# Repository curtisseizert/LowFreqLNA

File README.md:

# LowFreqLNA
A 0.01Hz-1+MHz low noise amplifier

Current Status
--------------
I have made two of these and have done a fair amount of testing to nail down root causes of some of the issues (see later in this readme) that have proven to be a bit of a nuisance. I am also moving things around a bit on the battery and battery charger boards to allow a board-to-board connection of the two and increase the clearance between the battery board and the amplifier board. I have also tested improvements to the input stage that significantly reduce the low frequency noise, lowering the 1/f corner to <1 Hz. These are detailed in the issues section #7.

1. Battery board revision: <b>complete</b>
2. Battery charger revision: <b>complete</b>
3. Low distortion buffer: back to drawing board
4. Main board revision: planning/schematic revision
5. BOM population: procrastinating

Introduction
------------

This repository contains the complete design files for a low noise AC coupled amplifier intended especially for characterization of 1/f noise of voltage references, DACs, etc. For broader applicability, it also has a reasonably high bandwidth of 2.5 MHz (measured, -3dB) at 60 or 80 dB gain, and about 1 MHz at 100 dB gain. Consistent with my primary use case for this amplifier, it has exceptionally low 1/f noise itself (measured at 3.2 nVRMS from 0.01-10 Hz) and a low broadband noise density of around 0.6 nV/rtHz. The quiescent current draw for the amplifier is about 30 mA, giving it a battery life of >100 h with the 4S 21700 Li batteries used to power the device. The project includes five PCBs:
(1) The main amplifier board
(2) The BMS board
(3) The SW board
(4) The front panel board
(5) The rear panel board/battery charger.

At present, I have hand assembled these using a converted toaster oven, which is a semi-onerous but doable-in-a-weekend task. As such, the BOMs are incomplete in all cases, which I will aim to rectify going forward. It is my hope that this will serve the needs of others designing voltage references, DACs, power supplies, etc. I may try to fix a couple things about this that have been bugging me, such as the lack of prefiltering and the antenna-like properties of the PP caps used in HP filters in the signal train. There is also a bit of room for reducing current draw. A fully differential version has been suggested, but if I work on that, I will make a separate repository for it.

The input stage is formed from a 24uF/100M RC high pass filter feeding a hybrid amplifier. The hybrid amplifier consists of 16 parallel JFE2140 dual JFETs in a cascode differential amplifier configuration. This drives an OPA140 op amp, which provides feedback via a 1k/2R divider to the inverting gate of the differential pair. The DC offset of the input stage is removed with a 2.2uF/10M HP filter. A switched gain stage amplifies the signal, which is HP filtered again to remove offsets and set the high-pass cutoff of the amplifier. The switched low-pass filtering is provided by two fourth-order butterworth filters in Sallen-Key topology. Switches select either one of these outputs or the unfiltered amplified signal to feed to the output stage.

A common problem with low-frequency AC coupled amplifiers is very long settling times when switching inputs. This is addressed with the "SETTLE" and "IN PROT" (Input protection) switches on the front panel. The former shorts the resistors of both of the post-input stage HP filter outputs with low-leakage MMBF4117 JFETs, and the latter shorts the input AC coupling filter by shorting the 100M resistor with a relay. The "IN PROT" switch also places a 6k04 resistor in series with the AC coupling filter to avoid large transients when switching between sources with different DC biases. With these switches, it is possible to take valid measurements down to 0.1 Hz with a minute or so of settling time and measurements down to 0.01 Hz with 5-10 minutes of settling time. Saturation of the amplifiers prior to both HP filters is detected with window comparators, which drive warning lights on the front panel. These features are meant to make it reasonably convenient to make low-level measurements and be confident the result is valid.

Electrical Characteristics
--------------------------

The following characteristics are taken from the one of these that I have fully assembled. Characterization was performed with a Digilent Analog Discovery Pro ADP3450 for bandwidths >10 kHz, a Keysight 34465A, and an HP3458A. Noise captures with the ADP3450 were digitized in Waveforms, exported, and transformed to the frequency domain using the SciPy Signal Python library in Spyder IDE. Captures with the HP3458A were taken using the PyVISA Python library for low frequency (50 SPS) digitization. The HP3458A was used for most low frequency work due to its superior isolation and common mode immunity. Bandwidth characterization was performed with the network analyzer utility in Waveforms for the ADP3450 and a 60dB attenuator. Gain calibration was performed by measuring the noise of a 6k04 resistor (9.97 nV/rtHz Johnson-Nyquist voltage noise density at 298k) comparing the bandwidth-limited RMS amplitude of the output signal to the theoretical value at the ambient temperature outside the amplifier. Linearity was checked by obtaining bandwidth-limited RMS amplitudes for a 240R resistor and a short, accounting for the RMS addition of the amplifier's own noise floor and that of the 240R resistor. The calibration resistors were 0.1%, 10 ppm/K thin film types. Quiescent current was measured by powering the amplifier with a Rigol DP832A DC power supply at +/-8V.

<table>
  <tr><td><b>Parameter</td><td><b>Condition</td><td><b>Result</td><td><b>Comment</td></tr>
  <tr><td>Voltage Noise Density</td><td>1 MHz</td><td>0.6 nV/rtHz</td><td>A</td></tr>
  <tr><td> </td><td>1 kHz</td><td>0.64 nV/rtHz</td><td>A</td></tr>
  <tr><td> </td><td>10 Hz</td><td>0.75 nV/rtHz</td><td>B</td></tr>
  <tr><td> </td><td>1 Hz</td><td>1.2 nV/rtHz</td><td>C</td></tr>
  <tr><td> </td><td>0.1 Hz</td><td>3.1 nV/rtHz</td><td>C</td></tr>
  <tr><td> </td><td>0.01 Hz</td><td>13.4 nV/rtHz</td><td>C,D</td></tr>
  <tr><td>Voltage Noise</td><td>0.1 Hz - 10 Hz</td><td>15 nV p-p</td><td>C</td></tr>
  <tr><td></td><td>0.01 Hz - 10 Hz</td><td>20 nV p-p</td><td>C</td></tr>
  <tr><td>Current Noise Density</td><td>0.1-1 Hz</td><td><2 fA/rtHz</td><td>E</td></tr>
  <tr><td>Input stage bias current</td><td></td><td>2.7 pA</td><td>F</td></tr>
  <tr><td>Input stage offset voltage</td><td></td><td>-94 uV</td><td>G</td></tr>
  <tr><td>-3dB Bandwidth</td><td>0R source impedance</td><td>2.8 MHz</td><td></td></tr>
  <tr><td>Input Capacitance</td><td>6k04 source impedance</td><td>140 pF</td><td>H</td></tr>
  <tr><td>10 kHz Low pass filter</td><td></td><td>4th order Butterworth</td><td></td></tr>
  <tr><td>10 Hz Low pass filter</td><td></td><td>4th order Butterworth</td><td></td></tr>
  <tr><td>THD</td><td>5 kHz</td><td><-70dB</td><td></td></tr>
  <tr><td>Quiescent Current</td><td>shorted input</td><td>30 mA</td><td></td></tr>
  <tr><td>Battery Capacity</td><td>Samsung 50S cells</td><td>5000 mA/h</td><td>nominal</td></tr>
  <tr><td>i_chg</td><td></td><td>2.7A</td><td></td></tr>
  <tr><td>Charger efficiency</td><td>V_Batt = 15V</td><td>98%</td><td>I</td></tr>
</table>

A: Full bandwidth, ADP-3450; B: 0.1-10 kHz bandwidth, ADP-3450; C: 0.01-10 Hz bandwidth, HP3458A; D: calc'd from measured value (9.5 nV/rtHz) and 3dB attenuation from HP filter; E: Calculated from open input VSD (100M resistor). Resulting noise was <0.1% from calculated value; F: Calculated from difference in offset voltage between 0R and 100M resistance to GND for input gate; G: Input gate shorted to GND; H: -3dB point with 6k04 resistor is 190 kHz. Primarily from board parasitics and RC damper; I: Measured on board, does not include cable losses

Spectra
-------

Application: Measuring voltage noise of voltage references
----------------------------------------------------------
Due to the low noise floor of the preamplifier, it can be used to easily measure the voltage noise of even the quietest (room temperature) references without error due to its own noise floor. Additionally, the use of polypropylene AC coupling capacitors with low dielectric absorption and the inclusion of the "SETTLE" feature allow measurement down to 10 mHz without excessive settling time. The plot below shows the voltage noise spectral density of several ADR1000-based 10-V references. Due to the high input impedance at low frequency, increasing the source impedance does not measurably change the gain of the amplifier. This is not the case with common 1000 uF/1k AC-coupled LNAs, which give considerable gain errors at even moderate source impedances (e.g., a 100 Ohm source impedance would give a gain error of 9.1%).

Issues
------

1. Input capacitance is higher than I'd like, which reduces the bandwidth with high impedance sources. Some of the capacitance is from board parasitics (ca. 100 pF), and some is from the R-C damper that is necessary to damp out oscillations with inductive sources (including most precision op amps). My plan to deal with this in the next revision is to modify the layout to reduce the board parasitics and switch in the R-C damper with an additional relay. Very little of the input capacitance is due to large Ciss of the paralleled JFETs as most of this presents as common mode capacitance and is bootstrapped by feedback. My target for input capacitance (with no R-C damper switched in) is 50 pF, but this is a lower priority than stability.
2. Second order (mostly) harmonic distortion of the ADA4622-2 buffer following the final HP filter stage leads to a DC offset term in the output. This is worst around 2 MHz and gets considerably worse with increasing ammplitude of the high frequency tone (it varies directly with the fourth power of the amplitude). The JFET switches are not a major issue (when SETTLE is off), which I have tested by removing them from the board. When SETTLE is on, it is worse, which negatively impacts settling time. As such, a 1 MHz sine wave amplitude modulated at 0.1 Hz will appear after 10 Hz LP filtering as a 0.1 Hz signal and harmonics, which is bad. The approach to this will be twofold: prefiltering and a composite buffer. Prefiltering will be described in #3. The composite buffer is a solution to a problem of a difficult convergence of design constraints: this buffer must have low Ib and current noise, reasonable common mode range (>+/-2.5V with 5.5V and -4.3V rails), low distortion at high frequency, and ability to operate on 10V total supply voltage with low quiescent current. To my knowledge, there are no monolithic amplifiers that satisfy these constraints. Without the high frequency distortion issue, only the ADA4622, OPAx191, and OPAx192 were good choices to my knowledge, but all of these led to the distortion-induced offset issue. In simulation, a dual JFET follower feeding an ADA4805 does well with a total quiescent current of about 1.1 mA and <0.1 dB peaking. I will prototype this block and test it before committing to the design for the next revision.
3. Amplifying signals at full bandwidth limits dynamic range for LF noise analyses. I will address this by filtering prior to the final gain stages, probably with a single-pole RC filter. Another solution would be to have the LP filter stages operate at gain >1, but I would prefer not to take this tack because it would mean the gain error of the amplifier is dependent on which LP filter stage is switched in.
4. Input protection switching is inconsistent due to contact bounce. I did not think this would be an issue with the one-shots used for relay switching, but it is. For now, connecting the K1_SW signal to both GND and 3V3 with 22k resistors does the trick, but this is not ideal, so I will implement a more robust dual-inverter debounce block for all the relay switches. In practice, however, only K1 seems to be affected by this issue due to it being switched differently on the front panel.
5. The 0804 (4x0402) resistor arrays are a PITA and almost always need to be fixed after reflow, so I'll replace those with 1206 (4x0603) arrays.
6. The 2.2 uF PP caps used in the HP filters seem to radiate, which requires shielding the input HP filter caps (these need to be PP for leakage). This shielding increases input capacitance (to ground), so I will replace the 2.2 uF caps with a few paralleled 470nF C0G capacitors, which have sufficiently low leakage to nullify the modest DC offsets following each stage, even with low frequency breakpoints.
7. The low frequency noise of the input stage is negatively impacted by the current noise of the mirror transistors. The fact that the low frequency noise is sub-optimal is evident from low frequency noise measurements of a pair of JFE2140s configured as source followers biased to the same drain current as a pair in the input stage. Because there are 16 such pairs in the LNA, the ratio of the NSD curves for this DUT and the noise floor should give a flat SNR of 12 dB, but this was not the case in the current revision. The most likely culprits to investigate were current noise from the NPN cascode transistor pair and current noise from the PNP current mirror transistor pair. Tests of the low frequency current noise of the NPN pair showed it was an unlikely culprit, accounting for perhaps 2% of the noise density at 10 mHz. Deletion of the current mirror pair, however, resolved the issue without any ill effects. This part was superfluous because the load seen by the collectors of the NPN cascode pair is the current mirror (or resistive loads) in parallel with 1/gm of the PNP folded cascode pair. With a collector current of ca. 100 uA, 1/gm is about 250R. With 330R resistive loads (i.e., shorting the collectors and emitters of the mirror transistors), the load drops from ~250R to ~142R, which still allows sufficiently high voltage gain at the emitters of the PNP pair to ensure they do not add significant noise. The effect of this modification on the low frequency noise is shown below.

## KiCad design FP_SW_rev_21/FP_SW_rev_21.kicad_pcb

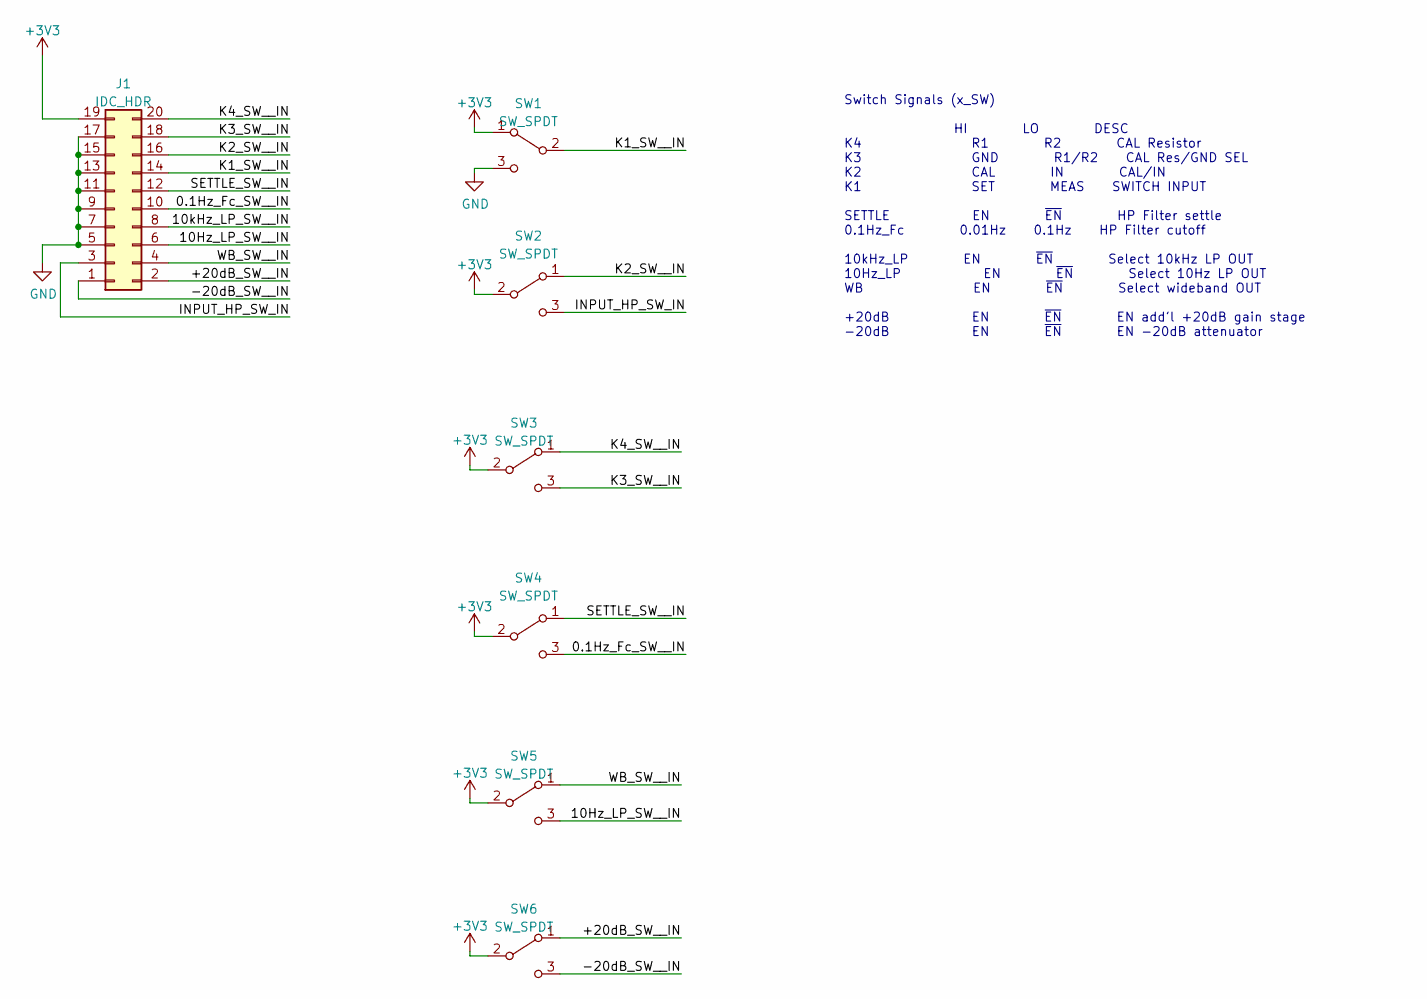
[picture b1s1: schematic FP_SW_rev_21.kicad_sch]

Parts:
J1: IDC_HDR; PinHeader_2x10_P1.27mm_Vertical
SW1, SW2, SW3, SW4, SW5, SW6: SW_SPDT; SW_SPDT_4.7_mm

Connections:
+3V3: J1.19, SW1.1 (A), SW2.2 (B), SW3.2 (B), SW4.2 (B), SW5.2 (B), SW6.2 (B)
/0.1Hz_Fc_SW__IN: J1.10, SW4.3 (C)
/10Hz_LP_SW__IN: J1.6, SW5.3 (C)
/10kHz_LP_SW__IN: J1.8
/+20dB_SW__IN: J1.2, SW6.1 (A)
/-20dB_SW__IN: J1.1, SW6.3 (C)
/INPUT_HP_SW_IN: J1.3, SW2.3 (C)
/K1_SW__IN: J1.14, SW1.2 (B)
/K2_SW__IN: J1.16, SW2.1 (A)
/K3_SW__IN: J1.18, SW3.3 (C)
/K4_SW__IN: J1.20, SW3.1 (A)
/SETTLE_SW__IN: J1.12, SW4.1 (A)
/WB_SW__IN: J1.4, SW5.1 (A)
GND: J1.5, J1.7, J1.9, J1.11, J1.13, J1.15, J1.17, SW1.3 (C)

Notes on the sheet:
Switch Signals (x_SW) HI LO DESC K4 R1 R2 CAL Resistor K3 GND R1/R2 CAL Res/GND SEL K2 CAL IN CAL/IN K1 SET MEAS SWITCH INPUT SETTLE EN ~{EN} HP Filter settle 0.1Hz_Fc 0.01Hz 0.1Hz HP Filter cutoff 10kHz_LP EN ~{EN} Select 10kHz LP OUT 10Hz_LP EN ~{EN} Select 10Hz LP OUT WB EN ~{EN} Select wideband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

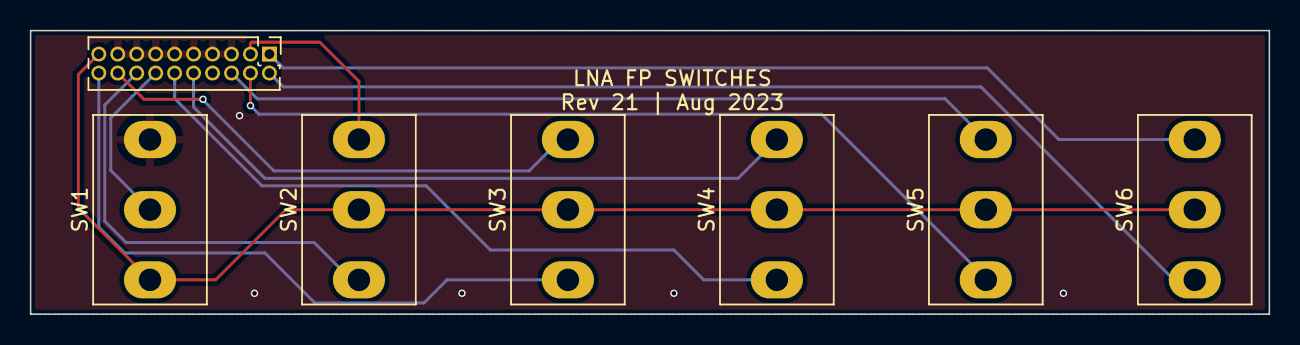
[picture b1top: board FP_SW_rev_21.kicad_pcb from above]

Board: 2 copper layers, 83.0 x 19.0 mm, 7 parts (0 on the bottom side), 13 nets.

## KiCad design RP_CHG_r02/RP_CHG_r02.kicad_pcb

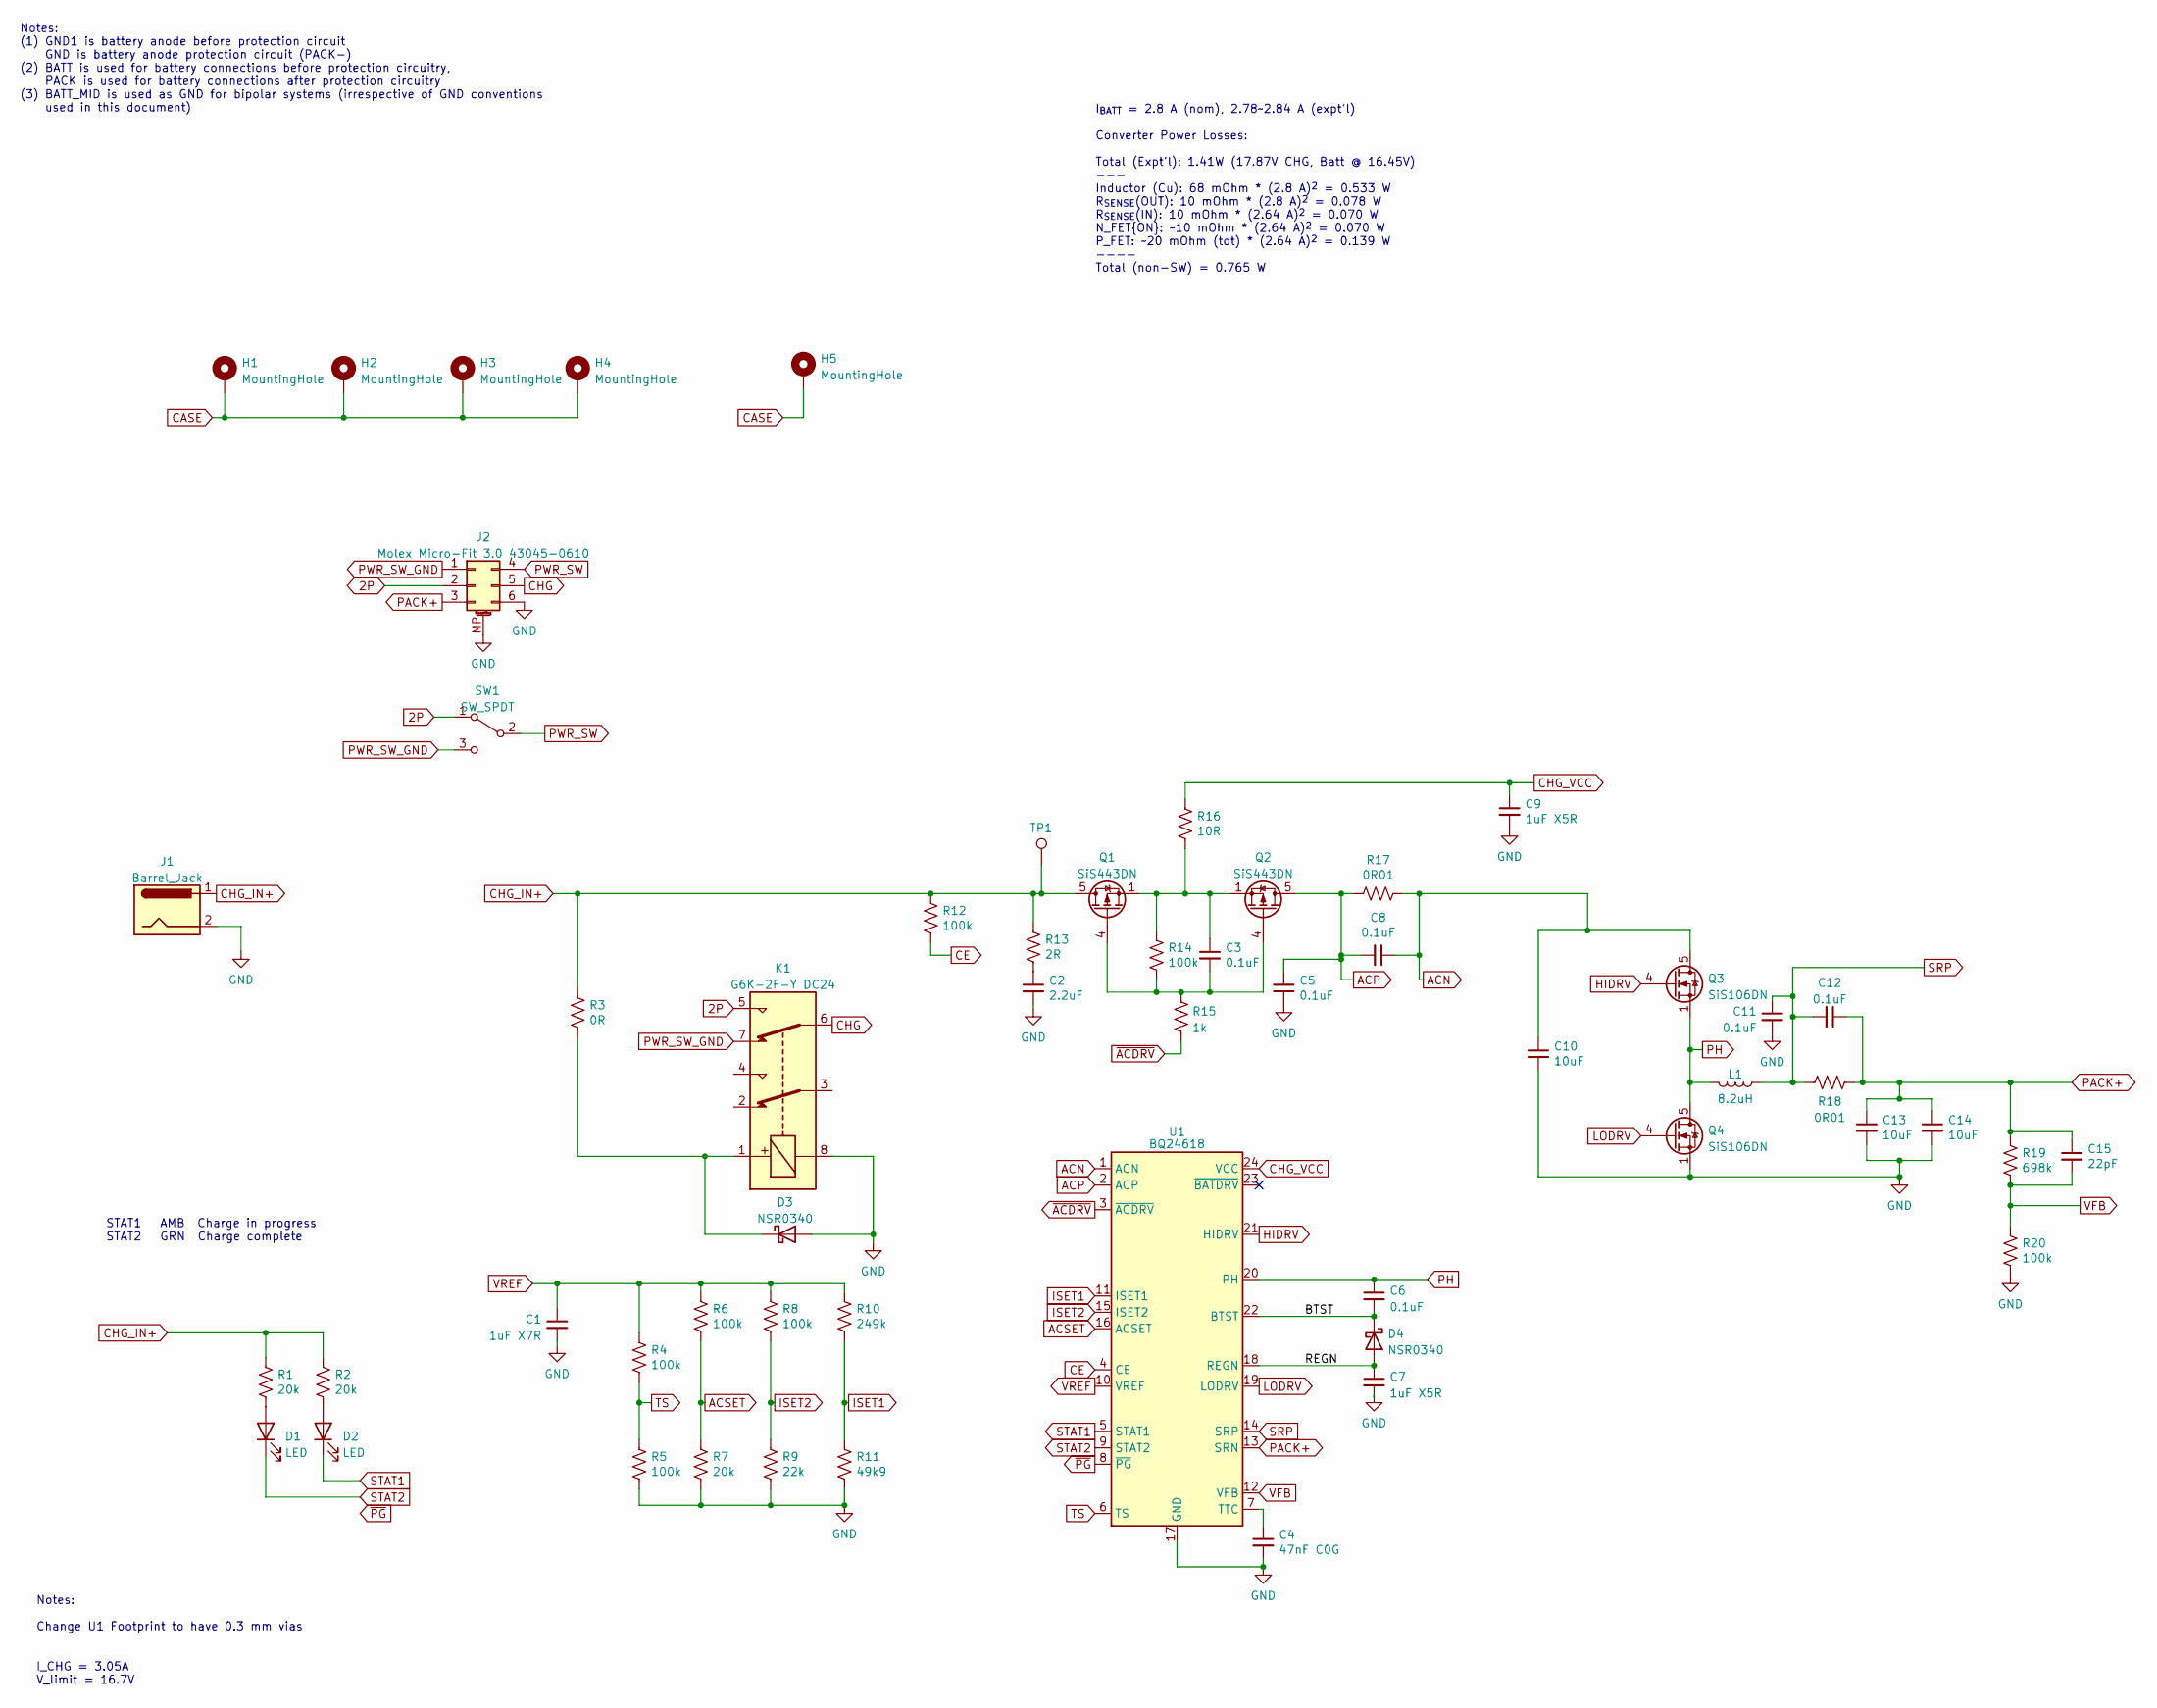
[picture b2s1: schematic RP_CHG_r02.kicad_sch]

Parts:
C1: 1uF X7R; C_0603_1608Metric_red_outline
C2: 2.2uF; C_1206_3216Metric_Red
C3, C5, C6, C8, C11, C12: 0.1uF; C_0402_1005Metric
C4: 47nF C0G; C_0805_2012Metric_Red_outline
C7, C9: 1uF X5R; C_0402_1005Metric
C10: 10uF; C_1210_3225Metric
C13, C14: 10uF; C_1206_3216Metric_Red
C15: 22pF; C_0603_1608Metric_red_outline
D1, D2: LED; LED_Osram_Lx_P47F_D2mm_ReverseMount
D3, D4: NSR0340; D_SOD-523
H1, H2, H3, H4: MountingHole; MountingHole_4.3mm_M4_ISO14580_Pad
H5: MountingHole; PanelCutout_6.5mm_PTH
J1: Barrel_Jack; BarrelJackDC_Switchcraft721_712
J2: Molex Micro-Fit 3.0 43045-0610; Molex_Micro-Fit_3.0_43045-0610_2x03-1MP_P3.00mm_Horizontal
K1: G6K-2F-Y DC24; Relay_DPDT_Omron_G6K-2F-Y
L1: 8.2uH; L_Vishay_IHLP-2525
Q1, Q2: SiS443DN; Vishay_PowerPAK_1212-8_Single
Q3, Q4: SiS106DN; Vishay_PowerPAK_1212-8_Single
R1, R2, R7: 20k; R_0402_1005Metric
R3: 0R; R_0603_1608Metric_red
R4, R5, R6, R8, R12, R14, R20: 100k; R_0402_1005Metric
R9: 22k; R_0402_1005Metric
R10: 249k; R_0402_1005Metric
R11: 49k9; R_0402_1005Metric
R13: 2R; R_0603_1608Metric_red
R15: 1k; R_0402_1005Metric
R16: 10R; R_0603_1608Metric_red
R17, R18: 0R01; R_1206_3216Metric
R19: 698k; R_0402_1005Metric
SW1: SW_SPDT; TestPoint_3Pads
TP1: TestPoint; TestPoint_Pad_D1.0mm
U1: BQ24618; HVQFN-24-1EP_4x4mm_P0.5mm_EP2.5x2.5mm

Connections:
2P: J2.2, K1.5, SW1.1 (A)
/BTST: C6.2, D4.1 (K), U1.22 (BTST)
/REGN: C7.1, D4.2 (A), U1.18 (REGN)
ACN: C8.1, C10.1, Q3.5 (D), R17.1, U1.1 (ACN)
ACP: C5.2, C8.2, Q2.5 (D), R17.2, U1.2 (ACP)
ACSET: R6.2, R7.1, U1.16 (ACSET)
CASE: H1.1, H2.1, H3.1, H4.1, H5.1
CE: R12.2, U1.4 (CE)
CHG: J2.5, K1.6
CHG_IN+: J1.1, Q1.5 (D), R1.1, R2.1, R3.2, R12.1, R13.1, TP1.1
CHG_VCC: C9.1, R16.2, U1.24 (VCC)
EP: C1.2, C2.2, C4.2, C5.1, C7.2, C9.2, C10.2, C11.2, C13.2, C14.2, D3.2 (A), J1.2, J2.6, J2.MP (MountPin), K1.8, Q4.1 (S), Q4.2 (S), Q4.3 (S), R5.2, R7.2, R9.2, R11.2, R20.1, U1.17 (GND), U1.25 (EP)
HIDRV: Q3.4 (G), U1.21 (HIDRV)
ISET1: R10.2, R11.1, U1.11 (ISET1)
ISET2: R8.2, R9.1, U1.15 (ISET2)
LODRV: Q4.4 (G), U1.19 (LODRV)
unnamed: C2.1, R13.2
unnamed: C3.1, Q1.1 (S), Q1.2 (S), Q1.3 (S), Q2.1 (S), Q2.2 (S), Q2.3 (S), R14.1, R16.1
unnamed: C3.2, Q1.4 (G), Q2.4 (G), R14.2, R15.1
unnamed: C4.1, U1.7 (TTC)
unnamed: D1.2 (A), R1.2
unnamed: D2.2 (A), R2.2
unnamed: D3.1 (K), K1.1, R3.1
PACK+: C12.1, C13.1, C14.1, C15.1, J2.3, R18.1, R19.2, U1.13 (SRN)
PH: C6.1, L1.2, Q3.1 (S), Q3.2 (S), Q3.3 (S), Q4.5 (D), U1.20 (PH)
PWR_SW: J2.4, SW1.2 (B)
PWR_SW_GND: J2.1, K1.7, SW1.3 (C)
SRP: C11.1, C12.2, L1.1, R18.2, U1.14 (SRP)
STAT1: D2.1 (K), U1.5 (STAT1)
STAT2: D1.1 (K), U1.9 (STAT2)
TS: R4.2, R5.1, U1.6 (TS)
VFB: C15.2, R19.1, R20.2, U1.12 (VFB)
VREF: C1.1, R4.1, R6.1, R8.1, R10.1, U1.10 (VREF)
~ACDRV: R15.2, U1.3 (~ACDRV)
~PG: U1.8 (~PG)

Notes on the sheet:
I_{BATT} = 2.8 A (nom), 2.78~2.84 A (expt'l) Converter Power Losses: Total (Expt'l): 1.41W (17.87V CHG, Batt @ 16.45V) --- Inductor (Cu): 68 mOhm * (2.8 A)^{2} = 0.533 W R_{SENSE}(OUT): 10 mOhm * (2.8 A)^{2} = 0.078 W R_{SENSE}(IN): 10 mOhm * (2.64 A)^{2} = 0.070 W N_FET{ON}: ~10 mOhm * (2.64 A)^{2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
I_CHG = 3.05A V_limit = 16.7V
Notes: (1) GND1 is battery anode before protection circuit GND is battery anode protection circuit (PACK-) (2) BATT is used for battery connections before protection circuitry, PACK is used for battery connections after protection circuitry (3) BATT_MID is used as GND for bipolar systems (irrespect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
STAT1 AMB Charge in progress STAT2 GRN Charge complete
Notes: Change U1 Footprint to have 0.3 mm vias

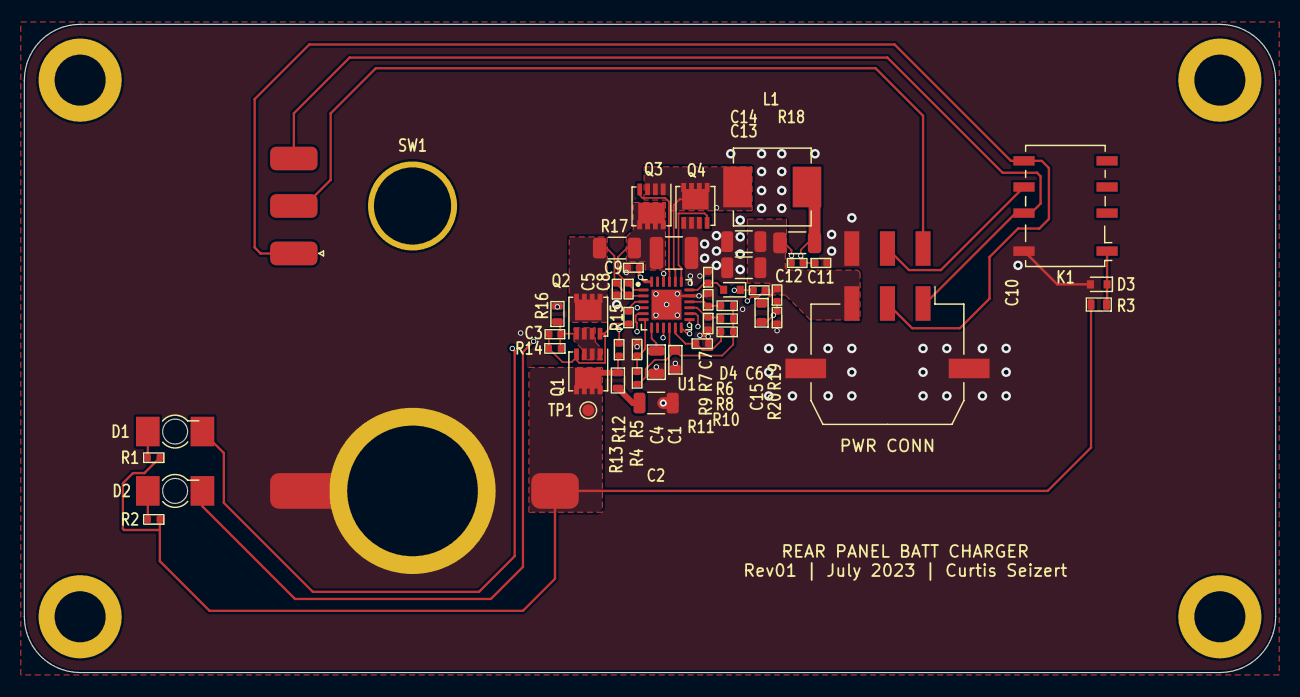
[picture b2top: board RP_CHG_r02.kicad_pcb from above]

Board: 4 copper layers, 105.4 x 54.6 mm, 55 parts (0 on the bottom side), 34 nets.

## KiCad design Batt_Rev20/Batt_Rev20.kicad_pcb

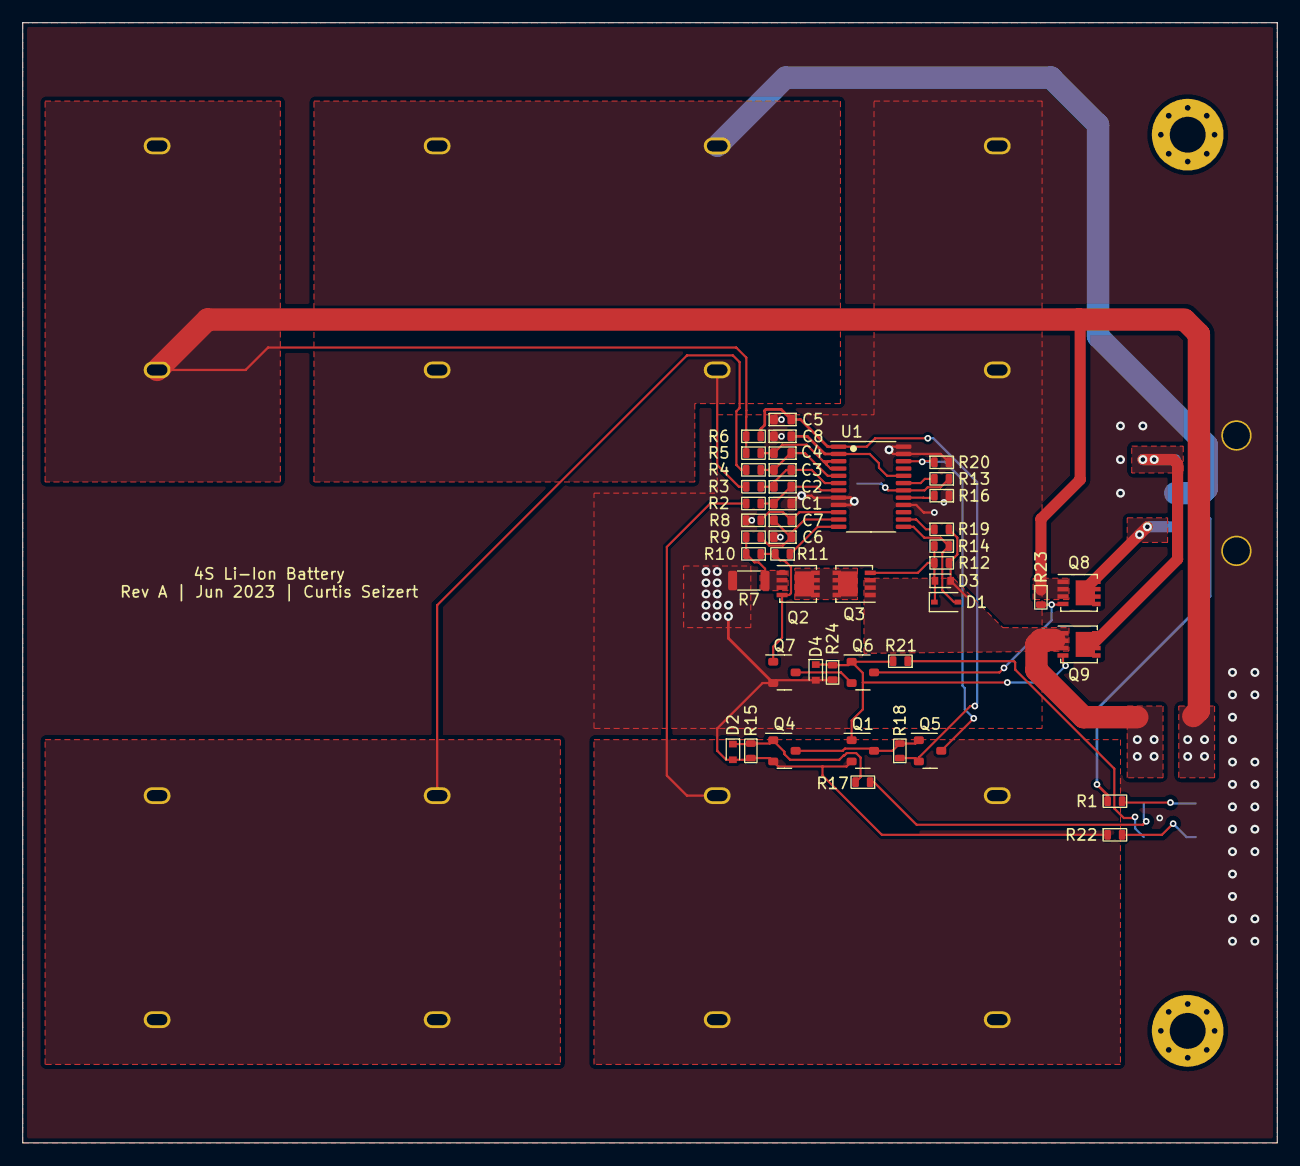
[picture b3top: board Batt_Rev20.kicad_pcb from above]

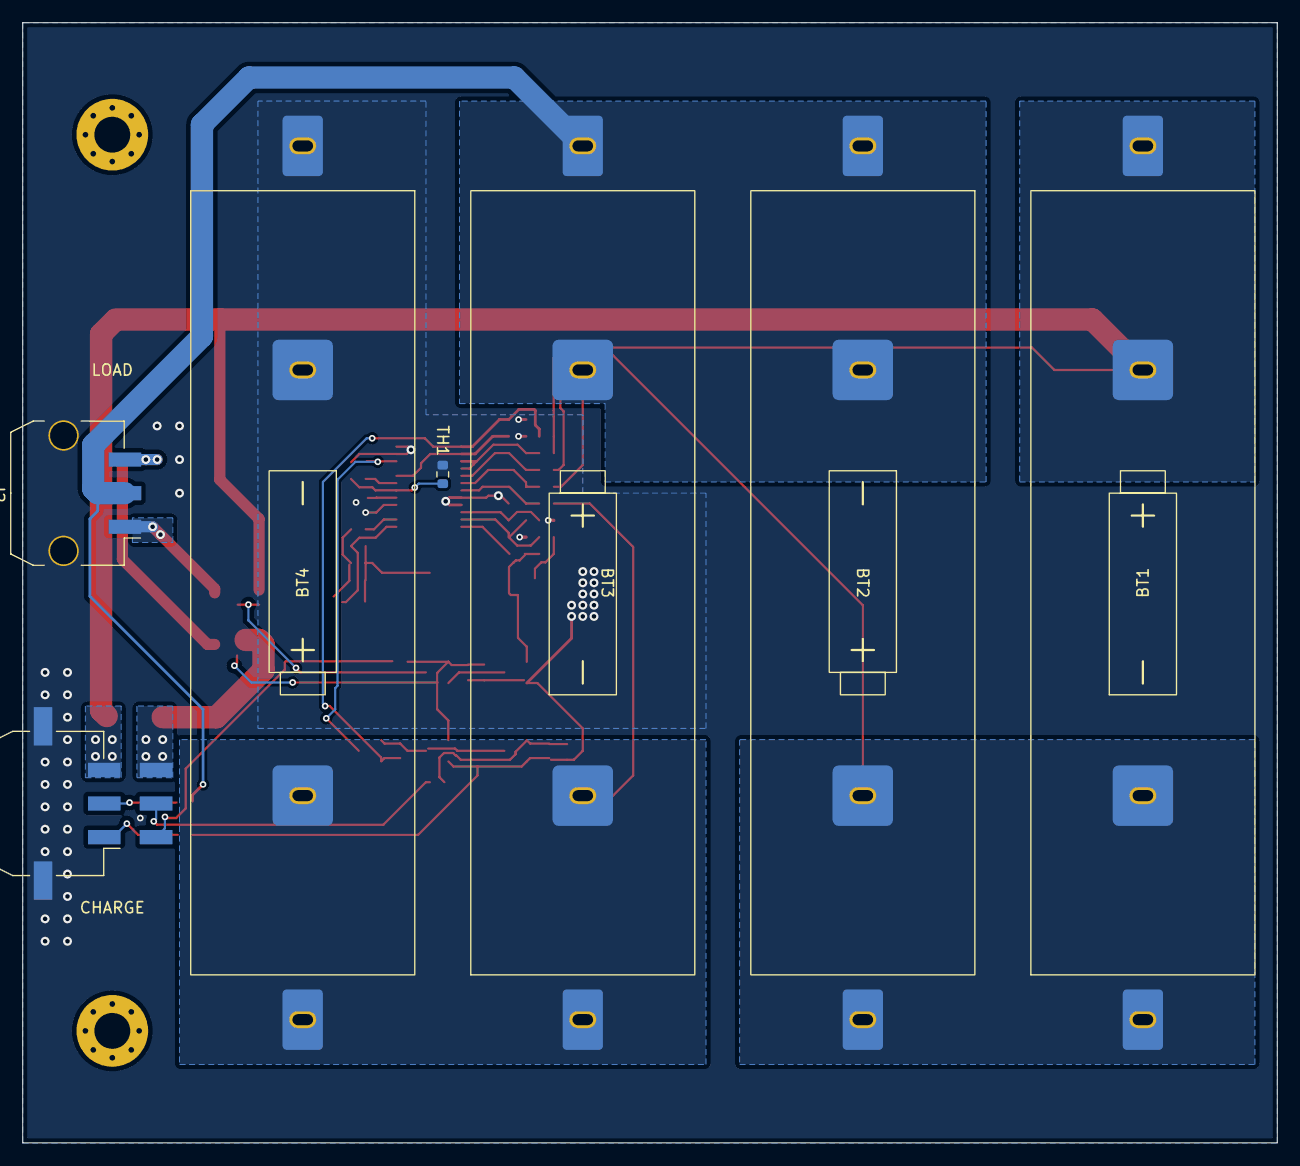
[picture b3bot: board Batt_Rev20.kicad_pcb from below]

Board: 2 copper layers, 112.0 x 100.0 mm, 56 parts (7 on the bottom side), 37 nets.

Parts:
BT1, BT2, BT3, BT4: Battery_Cell; BatteryHolder_Keystone246_21700
C1, C2, C3, C4, C5, C8: 1uF; C_0603_1608Metric_red_outline
C6, C7: 0.1uF; C_0603_1608Metric_red_outline
D1: RB751V40; D_SOD-323
D2, D3, D4: DZ2S100X0L; D_SOD-523
H1, H2: MountingHole; MountingHole_3.2mm_M3_Pad_Via
J1: Molex Micro-Fit 3.0 43045-0610; Molex_Micro-Fit_3.0_43045-0610_2x03-1MP_P3.00mm_Horizontal
J2: Micro-Fit 3.0 43650-0310; Molex_Micro-Fit_3.0_43650-0310_1x03-1MP_P3.00mm_Horizontal
NT1: Net-Tie_2; NetTie-2_SMD_Pad0.2mm
Q1, Q4, Q6, Q7: BSS123; SOT-23
Q2, Q3, Q9: SiS862ADN; Vishay_PowerPAK_1212-8_Single
Q5: BSS84; SOT-23
Q8: SiS443DN; Vishay_PowerPAK_1212-8_Single
R1, R6, R11, R14, R21, R22: 1k; R_0603_1608Metric_red
R2, R3, R4, R5: 33R; R_0603_1608Metric_red
R7: 0R01; R_1206_3216Metric_red
R8, R9: 100R; R_0603_1608Metric_red
R10, R12, R15, R18, R20, R23, R24: 1M; R_0603_1608Metric_red
R13, R17: 10k; R_0603_1608Metric_red
R16: 100k; R_0603_1608Metric_red
R19: 470k; R_0603_1608Metric_red
TH1: 103-AT; R_0603_1608Metric
U1: BQ77915-08; TSSOP-24_4.4x7.8mm_P0.65mm

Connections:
1P: BT3.1 (-), BT4.2 (+), R2.1
2P: BT2.1 (-), BT3.2 (+), J2.2, R1.1, R3.1
3P: BT1.1 (-), BT2.2 (+), R4.1
4P: NT1.2, R5.1, R6.1
/CHG_FET_G: D1.1 (K), D3.1 (K), Q3.4 (G), R12.1, R14.2
/DSG_FET_G: Q2.4 (G), Q7.1 (G), R10.1, R11.2
/PRES: Q5.3 (D), R20.1, U1.22 (PRES)
AVDD: C8.1, U1.2 (AVDD), U1.20 (CCFG)
BATT-: BT4.1 (-), C1.1, C5.2, C6.1, C8.2, D2.2 (A), D4.2 (A), J1.MP (MountPin), J2.MP (MountPin), Q1.2 (S), Q4.2 (S), Q7.2 (S), R7.1, R8.1, R15.2, R16.1, R20.2, R22.1, R24.2, TH1.2, U1.8 (VC0), U1.9 (VSS), U1.16 (CBI), U1.23 (CTRC), U1.24 (CTRD)
CHG: J1.5, R17.1
NMOS_G: D4.1 (K), Q1.1 (G), Q6.1 (G), Q9.4 (G), R21.2, R24.1
unnamed: C1.2, C2.1, R2.2, U1.7 (VC1)
unnamed: C2.2, C3.1, R3.2, U1.6 (VC2)
unnamed: C3.2, C4.1, R4.2, U1.5 (VC3)
unnamed: C4.2, R5.2, U1.3 (VC5), U1.4 (VC4)
unnamed: C6.2, C7.1, R9.1, U1.11 (SRN)
unnamed: C7.2, R8.2, U1.10 (SRP)
unnamed: D1.2 (A), R14.1, U1.13 (CHG)
unnamed: D2.1 (K), Q4.1 (G), R15.1, R17.2
unnamed: Q2.1 (S), Q2.2 (S), Q2.3 (S), R7.2, R9.2, R10.2
unnamed: Q2.5 (D), Q3.5 (D)
unnamed: Q1.3 (D), Q4.3 (D), Q5.1 (G), R18.2
unnamed: Q6.3 (D), Q8.4 (G), R23.2
unnamed: Q6.2 (S), Q7.3 (D)
unnamed: J1.2, R1.2
unnamed: R11.1, U1.12 (DSG)
unnamed: R13.1, TH1.1, U1.18 (TS)
unnamed: R13.2, U1.19 (VTB)
unnamed: R16.2, U1.17 (OCDP)
unnamed: R19.1, U1.14 (LD)
PACK+: BT1.2 (+), J1.3, NT1.1, Q8.1 (S), Q8.2 (S), Q8.3 (S), R23.1
PACK-: D3.2 (A), J1.6, Q3.1 (S), Q3.2 (S), Q3.3 (S), Q9.1 (S), Q9.2 (S), Q9.3 (S), R12.2, R19.2
PWR_SW: J1.4, R21.1
PWR_SW_GND: J1.1, R22.2
VDD: C5.1, Q5.2 (S), R6.2, R18.1, U1.1 (VDD)
V_{OUT}+: J2.1, Q8.5 (D)
V_{OUT}-: J2.3, Q9.5 (D)

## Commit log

2023-10-14 Second Commit
2023-10-14 Uploaded photos
2023-10-14 Update README.md
    Added picture
2023-11-09 Update README.md
    Added current status and issues sections, updated electrical characteristics with more extensive testing.
2023-11-12 Update README.md
    Fixed some typos and added status of individual tasks for next revision.
2024-01-31 Update README.md
    Added status updates
